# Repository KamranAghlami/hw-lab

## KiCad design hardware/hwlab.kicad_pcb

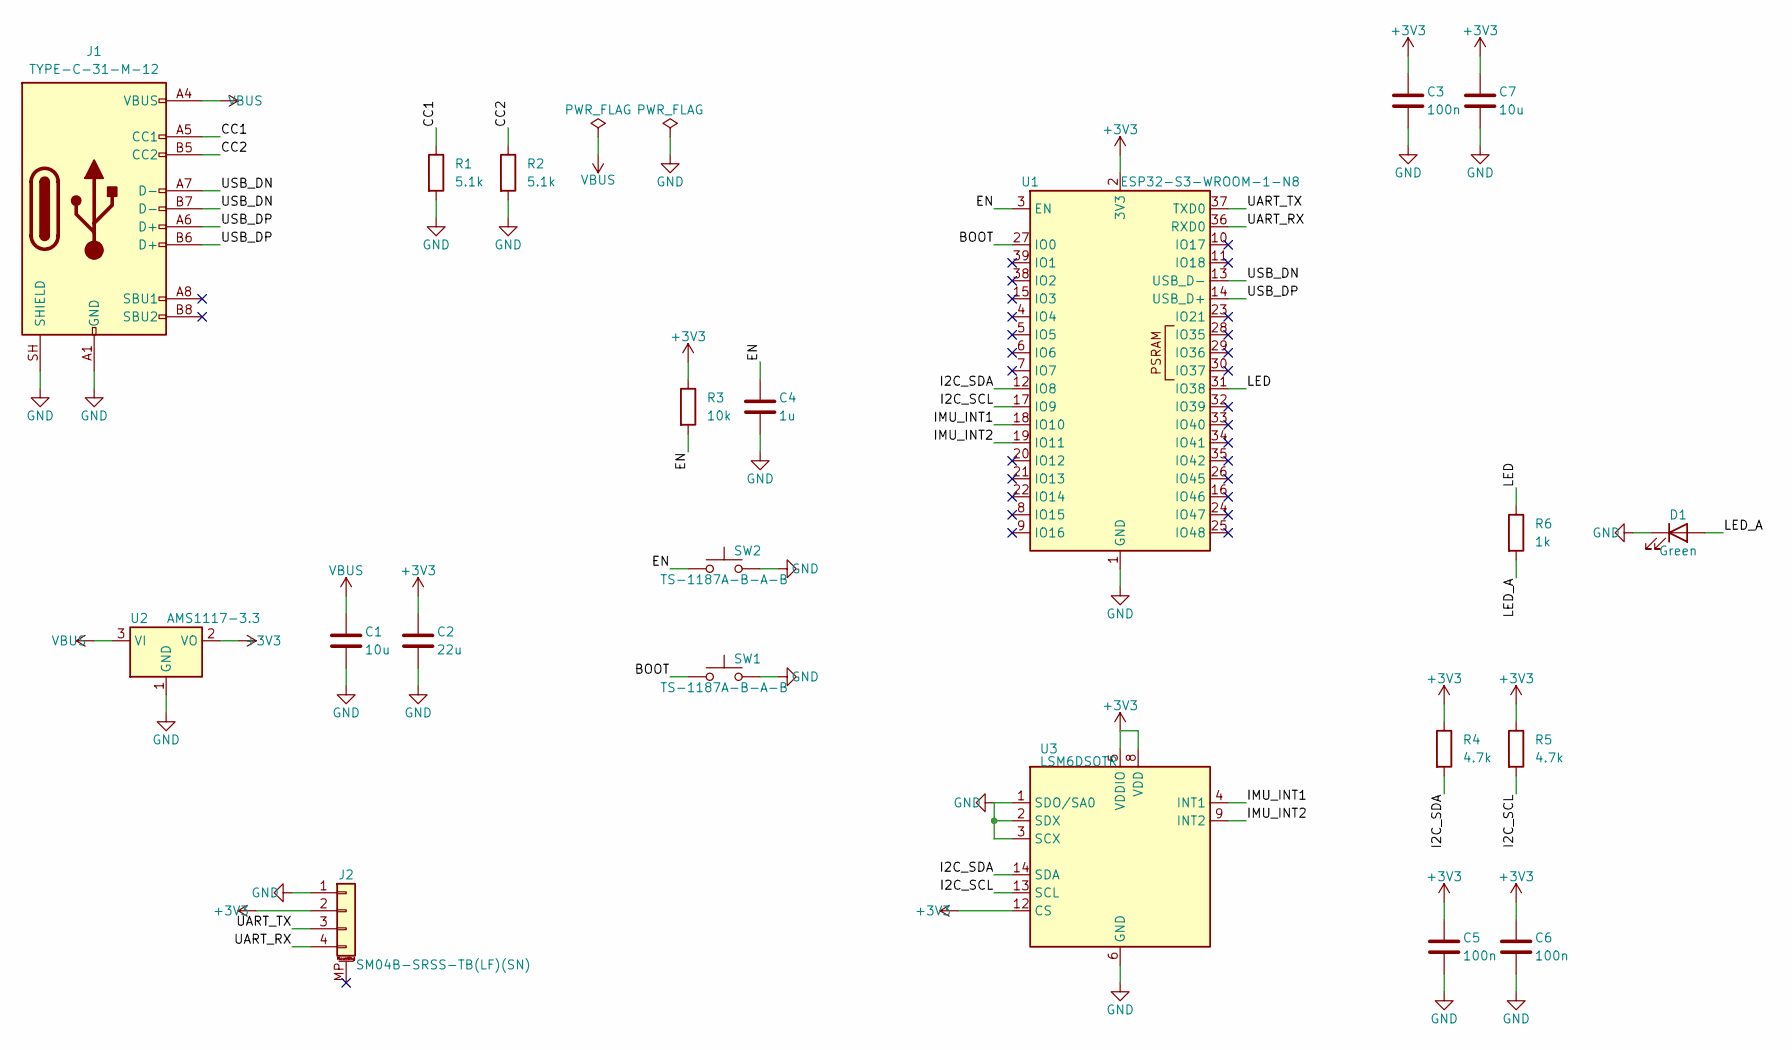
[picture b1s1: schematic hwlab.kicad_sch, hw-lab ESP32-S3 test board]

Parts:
C1, C7: 10u; C_0603_1608Metric; MPN CL10A106KP8NNNC; LCSC C19702
C2: 22u; C_0805_2012Metric; MPN CL21A226MAQNNNE; LCSC C45783
C3, C5, C6: 100n; C_0402_1005Metric; MPN CL05B104KO5NNNC; LCSC C1525
C4: 1u; C_0402_1005Metric; MPN CL05A105KA5NQNC; LCSC C52923
D1: Green; LED_0805_2012Metric; MPN KT-0805G; LCSC C2297
J1: TYPE-C-31-M-12; USB_C_Receptacle_HRO_TYPE-C-31-M-12; MPN TYPE-C-31-M-12; LCSC C165948
J2: SM04B-SRSS-TB(LF)(SN); JST_SH_SM04B-SRSS-TB_1x04-1MP_P1.00mm_Horizontal; MPN SM04B-SRSS-TB(LF)(SN); LCSC C160404
R1, R2: 5.1k; R_0402_1005Metric; MPN 0402WGF5101TCE; LCSC C25905
R3: 10k; R_0402_1005Metric; MPN 0402WGF1002TCE; LCSC C25744
R4, R5: 4.7k; R_0402_1005Metric; MPN 0402WGF4701TCE; LCSC C25900
R6: 1k; R_0402_1005Metric; MPN 0402WGF1001TCE; LCSC C11702
SW1, SW2: TS-1187A-B-A-B; SW_Push_1P1T_XKB_TS-1187A; MPN TS-1187A-B-A-B; LCSC C318884
U1: ESP32-S3-WROOM-1-N8; ESP32-S3-WROOM-1; MPN ESP32-S3-WROOM-1-N8; LCSC C2913198
U2: AMS1117-3.3; SOT-223-3_TabPin2; MPN AMS1117-3.3; LCSC C6186
U3: LSM6DSOTR; LGA-14_3x2.5mm_P0.5mm_LayoutBorder3x4y; MPN LSM6DSOTR; LCSC C2655100

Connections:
+3V3: C2.1, C3.1, C5.1, C6.1, C7.1, J2.2, R3.1, R4.1, R5.1, U1.2 (3V3), U2.2 (VO), U3.5 (VDDIO), U3.8 (VDD), U3.12 (CS)
/BOOT: SW1.1, U1.27 (IO0)
/CC1: J1.A5 (CC1), R1.1
/CC2: J1.B5 (CC2), R2.1
/EN: C4.1, R3.2, SW2.1, U1.3 (EN)
/I2C_SCL: R5.2, U1.17 (IO9), U3.13 (SCL)
/I2C_SDA: R4.2, U1.12 (IO8), U3.14 (SDA)
/IMU_INT1: U1.18 (IO10), U3.4 (INT1)
/IMU_INT2: U1.19 (IO11), U3.9 (INT2)
/LED: R6.1, U1.31 (IO38)
/LED_A: D1.2 (A), R6.2
/UART_RX: J2.4, U1.36 (RXD0)
/UART_TX: J2.3, U1.37 (TXD0)
/USB_DN: J1.A7 (D-), J1.B7 (D-), U1.13 (USB_D-)
/USB_DP: J1.A6 (D+), J1.B6 (D+), U1.14 (USB_D+)
GND: C1.2, C2.2, C3.2, C4.2, C5.2, C6.2, C7.2, D1.1 (K), J1.A1 (GND), J1.A12 (GND), J1.B1 (GND), J1.B12 (GND), J1.SH (SHIELD), J2.1, R1.2, R2.2, SW1.2, SW2.2, U1.1 (GND), U1.40 (GND), U1.41 (GND), U2.1 (GND), U3.1 (SDO/SA0), U3.2 (SDX), U3.3 (SCX), U3.6 (GND), U3.7 (GND)
VBUS: C1.1, J1.A4 (VBUS), J1.A9 (VBUS), J1.B4 (VBUS), J1.B9 (VBUS), U2.3 (VI)

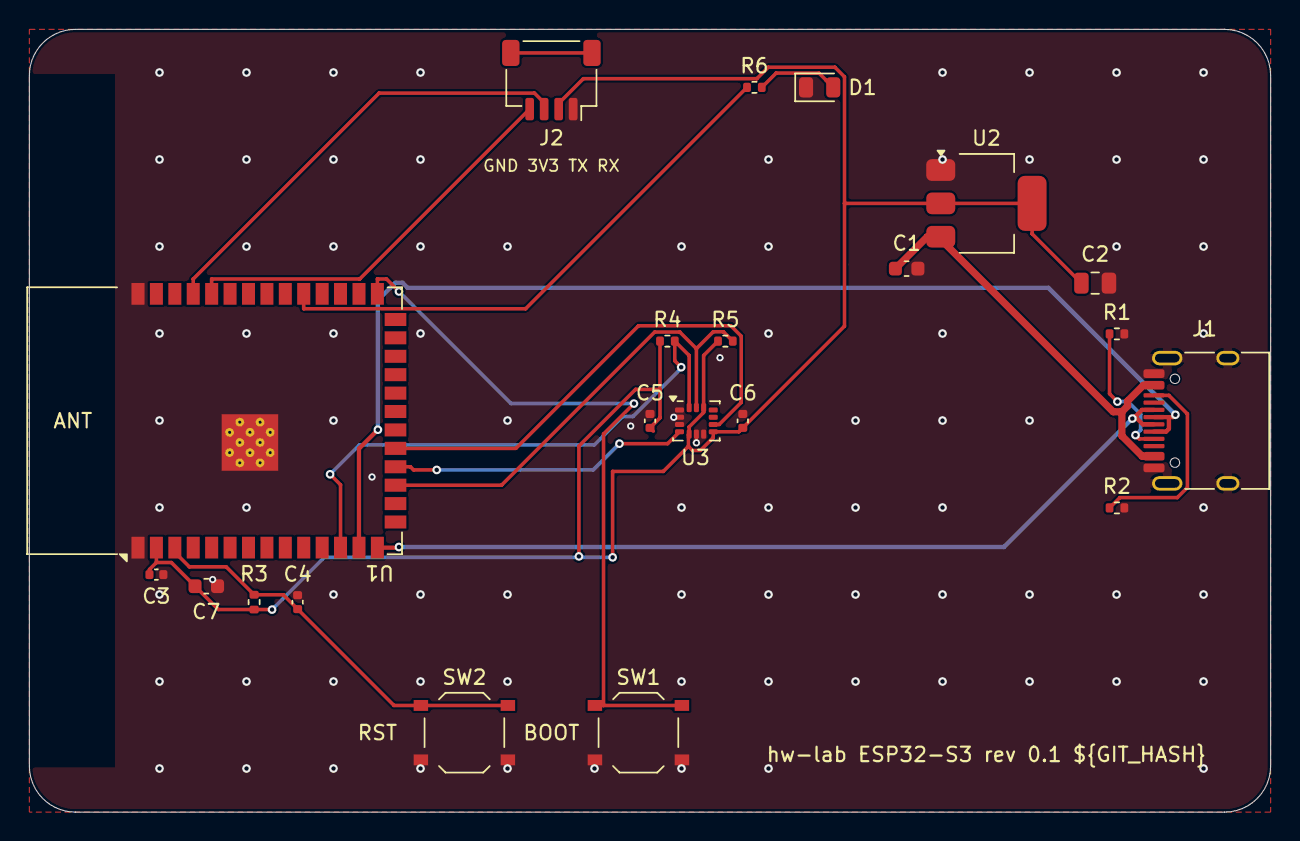
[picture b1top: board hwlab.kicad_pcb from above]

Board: 2 copper layers, 85.6 x 54.0 mm, 21 parts (0 on the bottom side), 17 nets.

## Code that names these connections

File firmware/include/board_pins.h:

// Generated by tools/pinmap.py from hardware/hwlab.kicad_sch. Do not edit by hand:
// change the schematic, then regenerate. CI fails if this drifts.
#pragma once

#define PIN_BOOT       0  // U1 pin 27 (IO0), net BOOT
#define PIN_I2C_SDA    8  // U1 pin 12 (IO8), net I2C_SDA
#define PIN_I2C_SCL    9  // U1 pin 17 (IO9), net I2C_SCL
#define PIN_IMU_INT1  10  // U1 pin 18 (IO10), net IMU_INT1
#define PIN_IMU_INT2  11  // U1 pin 19 (IO11), net IMU_INT2
#define PIN_USB_DN    19  // U1 pin 13 (USB_D-), net USB_DN
#define PIN_USB_DP    20  // U1 pin 14 (USB_D+), net USB_DP
#define PIN_LED       38  // U1 pin 31 (IO38), net LED
#define PIN_UART_TX   43  // U1 pin 37 (TXD0), net UART_TX
#define PIN_UART_RX   44  // U1 pin 36 (RXD0), net UART_RX
